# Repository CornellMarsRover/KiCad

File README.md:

# KiCad PCB Designs

This folder serves as the central repository for all KiCad PCB designs across multiple years.  
Each subfolder corresponds to a specific design cycle and contains all associated board files, schematics, and documentation.

## Notes

- All boards should be designed in **KiCad** using consistent design rules.  
- Follow best practices for manufacturability, testing, and revision tracking.  
- Keep README files updated in each yearly folder to summarize the boards within.

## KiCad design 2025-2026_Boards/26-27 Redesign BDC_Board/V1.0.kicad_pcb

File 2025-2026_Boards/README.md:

# Content for the markdown file
content = 2025-2026 Boards

This repository contains PCB designs for boards created in KiCad during the 2025-2026 design cycle.

## Overview

- **Design Tool:** KiCad  
- **Timeframe:** 2025–2026  
- **Purpose:** Centralized documentation and tracking of PCB projects made this year.

## Board Projects

- [ ] CANFD to USB board – Converts our USB connection to CANFD and vice versa to converse with the jetson
- [ ] PDB – Powers and distributes power through everything and can remotely turns on and off power to boards
- [ ] Temperature Regulation Board – Gets the temperature, displays it and turns on and off fans depending on the temperature 

## Notes

All designs should follow standard design rules and best practices for manufacturability and testing. Updates will be logged as the boards progress from schematic to layout to fabrication.

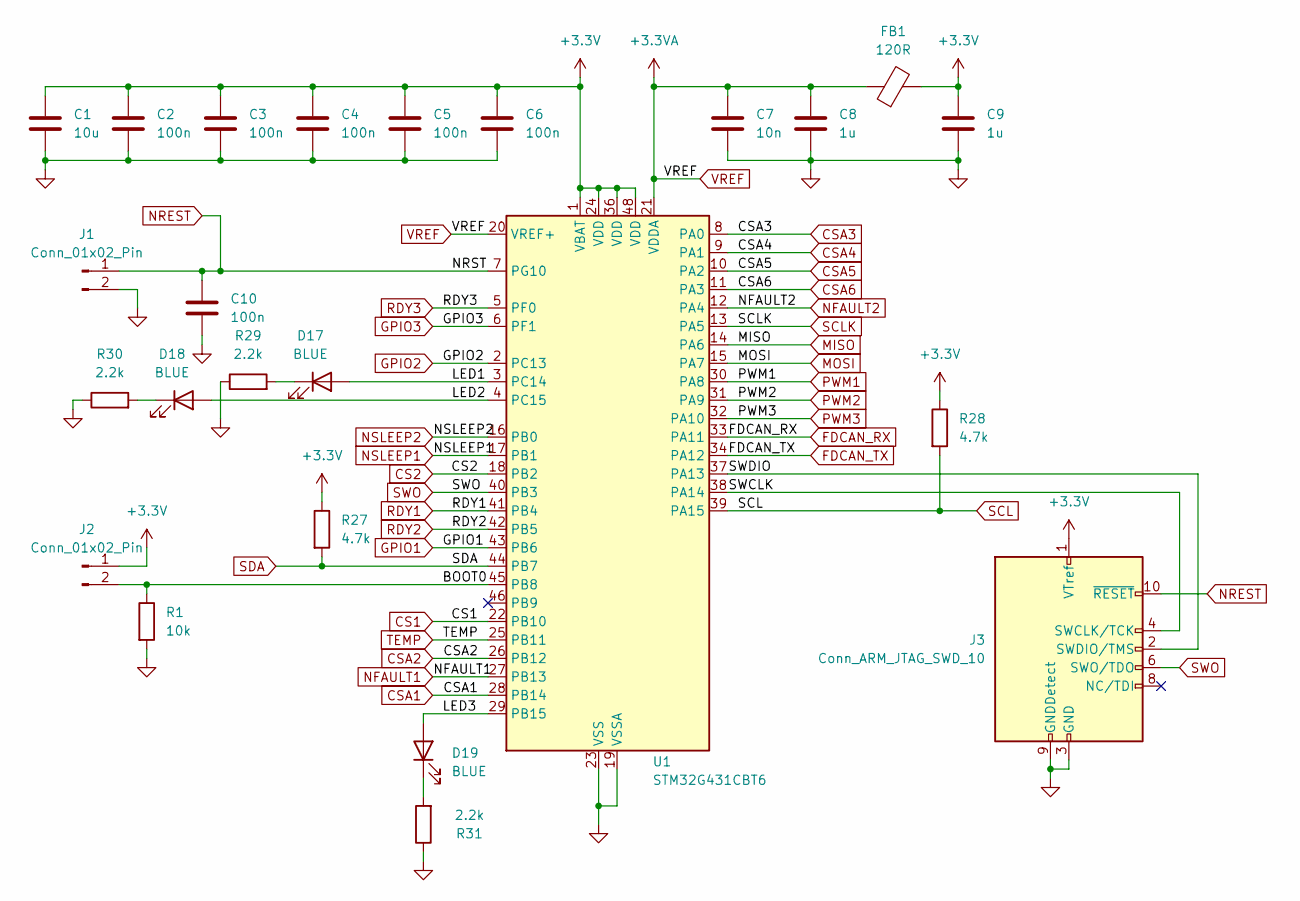
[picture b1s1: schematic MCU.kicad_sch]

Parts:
C1: 10u; C_0603_1608Metric
C2, C3, C4, C5, C6, C10: 100n; C_0402_1005Metric
C7: 10n; C_0402_1005Metric
C8, C9: 1u; C_0402_1005Metric
D17, D18, D19: BLUE; LED_0603_1608Metric
FB1: 120R; L_0603_1608Metric
J1: Conn_01x02_Pin; PinHeader_1x02_P2.54mm_Horizontal
J2: Conn_01x02_Pin; PinHeader_1x02_P2.54mm_Vertical
J3: Conn_ARM_JTAG_SWD_10; PinHeader_2x05_P1.27mm_Vertical
R1: 10k; R_0402_1005Metric
R27, R28: 4.7k; R_0402_1005Metric
R29, R30, R31: 2.2k; R_0402_1005Metric
U1: STM32G431CBT6; LQFP-48_7x7mm_P0.5mm

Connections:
+3.3V: C1.1, C2.1, C3.1, C4.1, C5.1, C6.1, C9.1, FB1.2, J2.1, J3.1 (VTref), R27.1, R28.1, U1.1 (VBAT), U1.24 (VDD), U1.36 (VDD), U1.48 (VDD); also elsewhere on the board
/MCU/BOOT0: J2.2, R1.1, U1.45 (PB8)
/MCU/LED1: D17.2 (A), U1.3 (PC14)
/MCU/LED2: D18.2 (A), U1.4 (PC15)
/MCU/LED3: D19.2 (A), U1.29 (PB15)
/MCU/SWCLK: J3.4 (SWCLK/TCK), U1.38 (PA14)
/MCU/SWDIO: J3.2 (SWDIO/TMS), U1.37 (PA13)
CS1: U1.22 (PB10); also elsewhere on the board
CS2: U1.18 (PB2); also elsewhere on the board
CSA1: U1.28 (PB14); also elsewhere on the board
CSA2: U1.26 (PB12); also elsewhere on the board
CSA3: U1.8 (PA0); also elsewhere on the board
CSA4: U1.9 (PA1); also elsewhere on the board
CSA5: U1.10 (PA2); also elsewhere on the board
CSA6: U1.11 (PA3); also elsewhere on the board
FDCAN_RX: U1.33 (PA11); also elsewhere on the board
FDCAN_TX: U1.34 (PA12); also elsewhere on the board
GND: C1.2, C2.2, C3.2, C4.2, C5.2, C6.2, C7.2, C8.2, C9.2, C10.2, J1.2, J3.3 (GND), J3.5 (GND), J3.9 (GNDDetect), R1.2, R29.1, R30.1, R31.1, U1.19 (VSSA), U1.23 (VSS), U1.35 (VSS), U1.47 (VSS); also elsewhere on the board
GPIO1: U1.43 (PB6); also elsewhere on the board
GPIO2: U1.2 (PC13); also elsewhere on the board
GPIO3: U1.6 (PF1); also elsewhere on the board
MISO: U1.14 (PA6); also elsewhere on the board
MOSI: U1.15 (PA7); also elsewhere on the board
NFAULT1: U1.27 (PB13); also elsewhere on the board
NFAULT2: U1.12 (PA4); also elsewhere on the board
NREST: C10.1, J1.1, J3.10 (~RESET), U1.7 (PG10); also elsewhere on the board
NSLEEP1: U1.17 (PB1); also elsewhere on the board
NSLEEP2: U1.16 (PB0); also elsewhere on the board
unnamed: D17.1 (K), R29.2
unnamed: D18.1 (K), R30.2
unnamed: D19.1 (K), R31.2
PWM1: U1.30 (PA8); also elsewhere on the board
PWM2: U1.31 (PA9); also elsewhere on the board
PWM3: U1.32 (PA10); also elsewhere on the board
RDY1: U1.41 (PB4); also elsewhere on the board
RDY2: U1.42 (PB5); also elsewhere on the board
RDY3: U1.5 (PF0); also elsewhere on the board
SCL: R28.2, U1.39 (PA15); also elsewhere on the board
SCLK: U1.13 (PA5); also elsewhere on the board
SDA: R27.2, U1.44 (PB7); also elsewhere on the board
SWO: J3.6 (SWO/TDO), U1.40 (PB3)
TEMP: U1.25 (PB11); also elsewhere on the board
VREF: C7.1, C8.1, FB1.1, U1.20 (VREF+), U1.21 (VDDA)

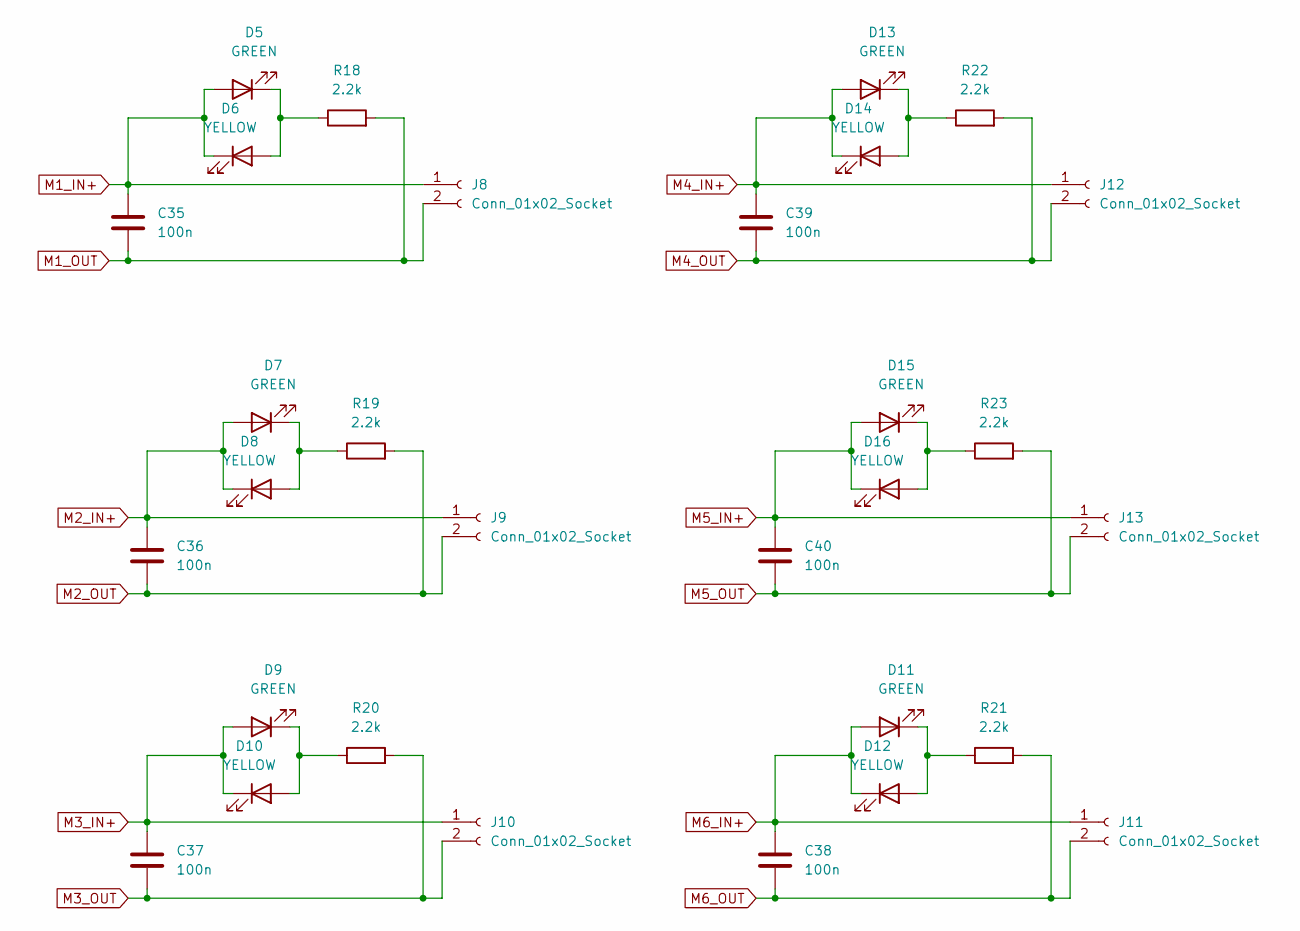
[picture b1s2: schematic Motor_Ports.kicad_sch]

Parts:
C35, C36, C37, C38, C39, C40: 100n; C_1206_3216Metric
D5, D7, D9, D11, D13, D15: GREEN; LED_0603_1608Metric
D6, D8, D10, D12, D14, D16: YELLOW; LED_0603_1608Metric
J8, J9, J10, J11, J12, J13: Conn_01x02_Socket; AMASS_XT30PW-M_1x02_P2.50mm_Horizontal
R18, R19, R20, R21, R22, R23: 2.2k; R_0402_1005Metric

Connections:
M1_IN+: C35.1, D5.2 (A), D6.1 (K), J8.1; also elsewhere on the board
M1_OUT: C35.2, J8.2, R18.2; also elsewhere on the board
M2_IN+: C36.1, D7.2 (A), D8.1 (K), J9.1; also elsewhere on the board
M2_OUT: C36.2, J9.2, R19.2; also elsewhere on the board
M3_IN+: C37.1, D9.2 (A), D10.1 (K), J10.1; also elsewhere on the board
M3_OUT: C37.2, J10.2, R20.2; also elsewhere on the board
M4_IN+: C39.1, D13.2 (A), D14.1 (K), J12.1; also elsewhere on the board
M4_OUT: C39.2, J12.2, R22.2; also elsewhere on the board
M5_IN+: C40.1, D15.2 (A), D16.1 (K), J13.1; also elsewhere on the board
M5_OUT: C40.2, J13.2, R23.2; also elsewhere on the board
M6_IN+: C38.1, D11.2 (A), D12.1 (K), J11.1; also elsewhere on the board
M6_OUT: C38.2, J11.2, R21.2; also elsewhere on the board
unnamed: D5.1 (K), D6.2 (A), R18.1
unnamed: D7.1 (K), D8.2 (A), R19.1
unnamed: D9.1 (K), D10.2 (A), R20.1
unnamed: D11.1 (K), D12.2 (A), R21.1
unnamed: D13.1 (K), D14.2 (A), R22.1
unnamed: D15.1 (K), D16.2 (A), R23.1

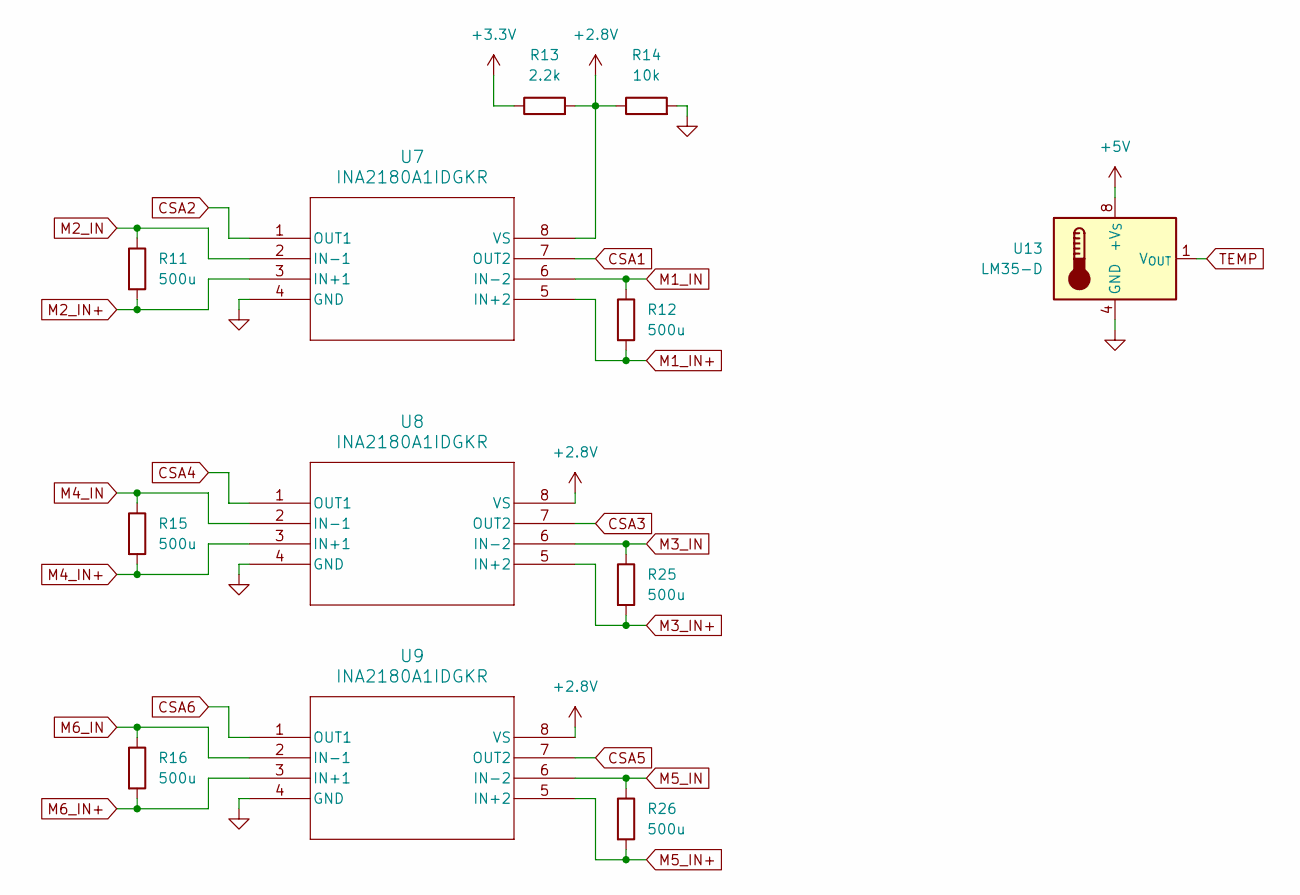
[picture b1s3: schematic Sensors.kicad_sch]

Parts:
R11, R12, R15, R16, R25, R26: 500u; R_0805_2012Metric
R13: 2.2k; R_0402_1005Metric
R14: 10k; R_0402_1005Metric
U7, U8, U9: INA2180A1IDGKR; VSSOP-8_3x3mm_P0.65mm
U13: LM35-D; SOIC-8_3.9x4.9mm_P1.27mm

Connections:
+2.8V: R13.2, R14.1, U7.8 (VS), U8.8 (VS), U9.8 (VS)
+3.3V: R13.1; also elsewhere on the board
+5V: U13.8 (+V_{S}); also elsewhere on the board
CSA1: U7.7 (OUT2); also elsewhere on the board
CSA2: U7.1 (OUT1); also elsewhere on the board
CSA3: U8.7 (OUT2); also elsewhere on the board
CSA4: U8.1 (OUT1); also elsewhere on the board
CSA5: U9.7 (OUT2); also elsewhere on the board
CSA6: U9.1 (OUT1); also elsewhere on the board
GND: R14.2, U7.4 (GND), U8.4 (GND), U9.4 (GND), U13.4 (GND); also elsewhere on the board
M1_IN: R12.1, U7.6 (IN-2); also elsewhere on the board
M1_IN+: R12.2, U7.5 (IN+2); also elsewhere on the board
M2_IN: R11.1, U7.2 (IN-1); also elsewhere on the board
M2_IN+: R11.2, U7.3 (IN+1); also elsewhere on the board
M3_IN: R25.1, U8.6 (IN-2); also elsewhere on the board
M3_IN+: R25.2, U8.5 (IN+2); also elsewhere on the board
M4_IN: R15.1, U8.2 (IN-1); also elsewhere on the board
M4_IN+: R15.2, U8.3 (IN+1); also elsewhere on the board
M5_IN: R26.1, U9.6 (IN-2); also elsewhere on the board
M5_IN+: R26.2, U9.5 (IN+2); also elsewhere on the board
M6_IN: R16.1, U9.2 (IN-1); also elsewhere on the board
M6_IN+: R16.2, U9.3 (IN+1); also elsewhere on the board
TEMP: U13.1 (V_{OUT}); also elsewhere on the board

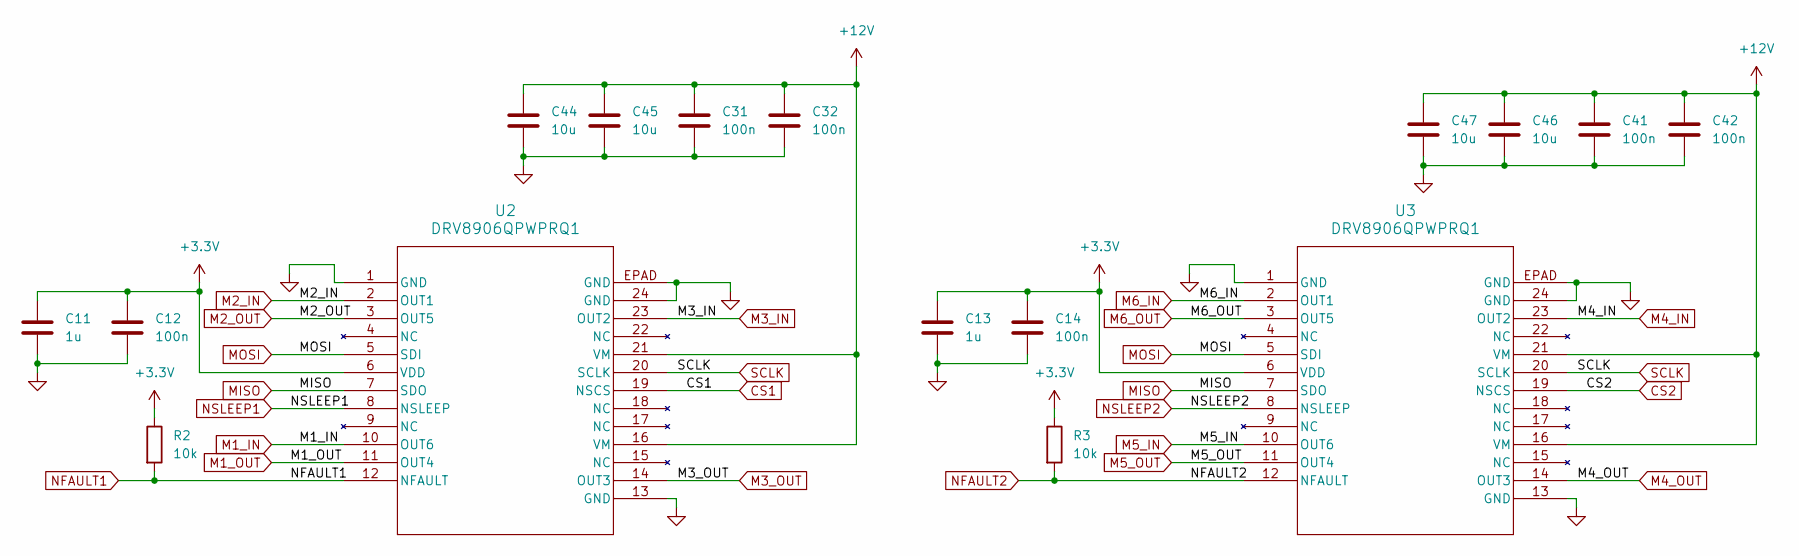
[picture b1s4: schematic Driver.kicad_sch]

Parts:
C11, C13: 1u; C_0402_1005Metric
C12, C14, C31, C32, C41, C42: 100n; C_0402_1005Metric
C44, C45, C46, C47: 10u; C_0603_1608Metric
R2, R3: 10k; R_0402_1005Metric
U2, U3: DRV8906QPWPRQ1; HTSSOP24_PWP_TEX

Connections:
+3.3V: C11.1, C12.1, C13.1, C14.1, R2.1, R3.1, U2.6 (VDD), U3.6 (VDD); also elsewhere on the board
+12V: C31.1, C32.1, C41.1, C42.1, C44.1, C45.1, C46.1, C47.1, U2.16 (VM), U2.21 (VM), U3.16 (VM), U3.21 (VM); also elsewhere on the board
CS1: U2.19 (NSCS); also elsewhere on the board
CS2: U3.19 (NSCS); also elsewhere on the board
GND: C11.2, C12.2, C13.2, C14.2, C31.2, C32.2, C41.2, C42.2, C44.2, C45.2, C46.2, C47.2, U2.1 (GND), U2.13 (GND), U2.24 (GND), U2.EPAD (GND), U3.1 (GND), U3.13 (GND), U3.24 (GND), U3.EPAD (GND); also elsewhere on the board
M1_IN: U2.10 (OUT6); also elsewhere on the board
M1_OUT: U2.11 (OUT4); also elsewhere on the board
M2_IN: U2.2 (OUT1); also elsewhere on the board
M2_OUT: U2.3 (OUT5); also elsewhere on the board
M3_IN: U2.23 (OUT2); also elsewhere on the board
M3_OUT: U2.14 (OUT3); also elsewhere on the board
M4_IN: U3.23 (OUT2); also elsewhere on the board
M4_OUT: U3.14 (OUT3); also elsewhere on the board
M5_IN: U3.10 (OUT6); also elsewhere on the board
M5_OUT: U3.11 (OUT4); also elsewhere on the board
M6_IN: U3.2 (OUT1); also elsewhere on the board
M6_OUT: U3.3 (OUT5); also elsewhere on the board
MISO: U2.7 (SDO), U3.7 (SDO); also elsewhere on the board
MOSI: U2.5 (SDI), U3.5 (SDI); also elsewhere on the board
NFAULT1: R2.2, U2.12 (NFAULT); also elsewhere on the board
NFAULT2: R3.2, U3.12 (NFAULT); also elsewhere on the board
NSLEEP1: U2.8 (NSLEEP); also elsewhere on the board
NSLEEP2: U3.8 (NSLEEP); also elsewhere on the board
SCLK: U2.20 (SCLK), U3.20 (SCLK); also elsewhere on the board

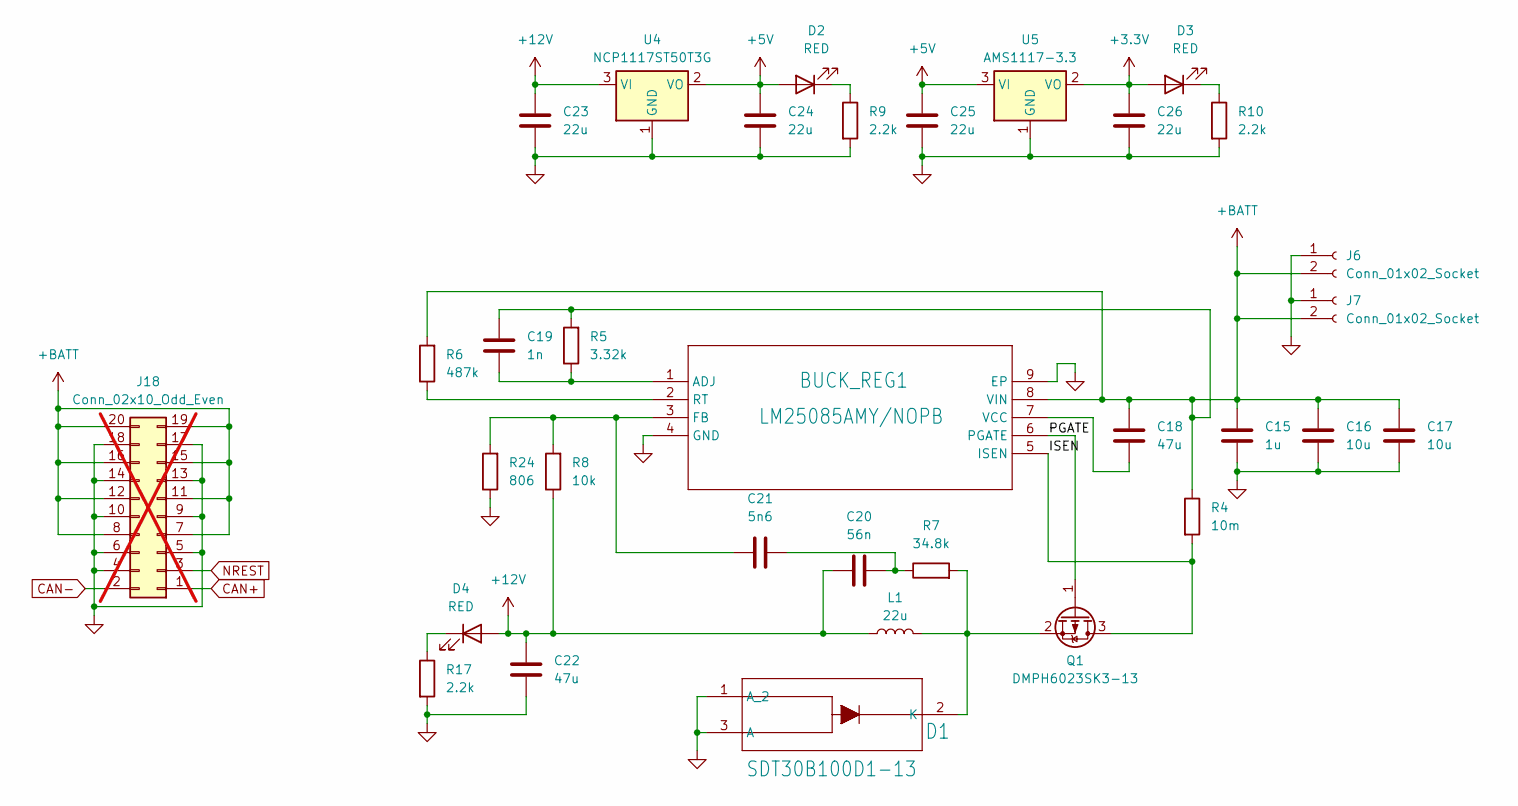
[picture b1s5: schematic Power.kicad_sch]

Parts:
BUCK_REG1: LM25085AMY/NOPB; HVSSOP-8-1EP_3x3mm_P0.65mm_EP1.57x1.89mm
C15: 1u; C_0603_1608Metric
C16, C17: 10u; C_1206_3216Metric
C18, C22: 47u; C_1206_3216Metric
C19: 1n; C_0603_1608Metric
C20: 56n; C_0603_1608Metric
C21: 5n6; C_0603_1608Metric
C23, C24, C25, C26: 22u; C_0805_2012Metric
D1: SDT30B100D1-13; TO-252-2
D2, D3, D4: RED; LED_0603_1608Metric
J6, J7: Conn_01x02_Socket; AMASS_XT30PW-M_1x02_P2.50mm_Horizontal
J18: Conn_02x10_Odd_Even; PinSocket_2x10_P2.54mm_Horizontal; not fitted
L1: 22u; IND_A-4R7M
Q1: DMPH6023SK3-13; TO-252-2
R4: 10m; R_1206_3216Metric
R5: 3.32k; R_1206_3216Metric
R6: 487k; R_0603_1608Metric
R7: 34.8k; R_0603_1608Metric
R8: 10k; R_0603_1608Metric
R9, R10, R17: 2.2k; R_0402_1005Metric
R24: 806; R_0603_1608Metric
U4: NCP1117ST50T3G; SOT-223-3_TabPin2
U5: AMS1117-3.3; SOT-223-3_TabPin2

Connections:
+3.3V: C26.1, D3.2 (A), U5.2 (VO); also elsewhere on the board
+5V: C24.1, C25.1, D2.2 (A), U4.2 (VO), U5.3 (VI); also elsewhere on the board
+12V: C20.1, C22.1, C23.1, D4.2 (A), L1.1, R8.1, U4.3 (VI); also elsewhere on the board
+BATT: BUCK_REG1.8 (VIN), C15.1, C16.1, C17.1, C18.1, C19.1, J6.2, J7.2, J18.7, J18.8, J18.11, J18.12, J18.15, J18.16, J18.19, J18.20, R4.1, R5.2, R6.2
/Power/PGATE: BUCK_REG1.6 (PGATE), Q1.1 (G)
CAN+: J18.1; also elsewhere on the board
CAN-: J18.2; also elsewhere on the board
GND: BUCK_REG1.4 (GND), BUCK_REG1.9 (EP), C15.2, C16.2, C17.2, C22.2, C23.2, C24.2, C25.2, C26.2, D1.1 (A_2), D1.3 (A), J6.1, J7.1, J18.4, J18.5, J18.6, J18.9, J18.10, J18.13, J18.14, J18.17, J18.18, R9.2, R10.2, R17.2, R24.1, U4.1 (GND), U5.1 (GND); also elsewhere on the board
NREST: J18.3; also elsewhere on the board
unnamed: BUCK_REG1.1 (ADJ), C19.2, R5.1
unnamed: BUCK_REG1.3 (FB), C21.1, R8.2, R24.2
unnamed: BUCK_REG1.2 (RT), R6.1
unnamed: BUCK_REG1.7 (VCC), C18.2
unnamed: C20.2, C21.2, R7.1
unnamed: D2.1 (K), R9.1
unnamed: D3.1 (K), R10.1
unnamed: D4.1 (K), R17.1

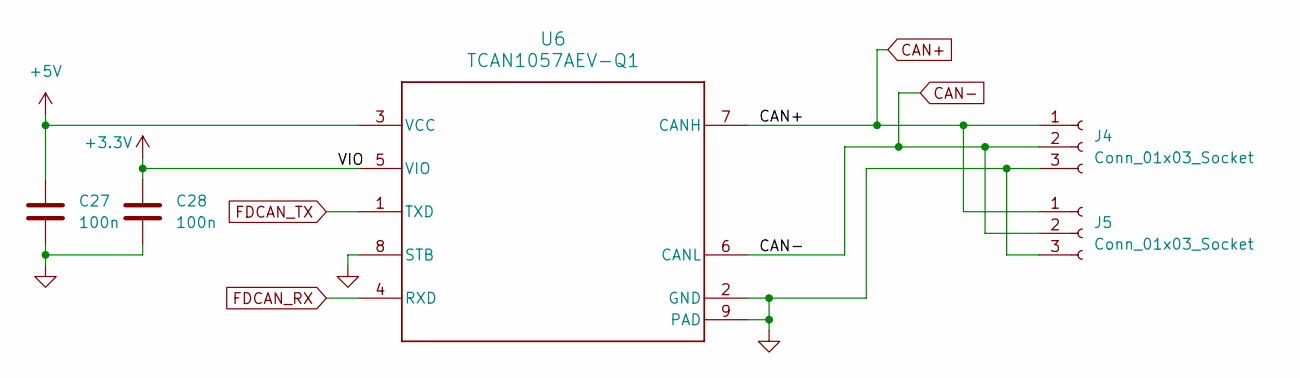
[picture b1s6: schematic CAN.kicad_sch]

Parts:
C27, C28: 100n; C_0402_1005Metric
J4, J5: Conn_01x03_Socket; JST_PH_S3B-PH-SM4-TB_1x03-1MP_P2.00mm_Horizontal
U6: TCAN1057AEV-Q1; SOIC-8_3.9x4.9mm_P1.27mm; MPN TCAN1057AEVDRQ1

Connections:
+3.3V: C28.1, U6.5 (VIO); also elsewhere on the board
+5V: C27.1, U6.3 (VCC); also elsewhere on the board
CAN+: J4.1, J5.1, U6.7 (CANH); also elsewhere on the board
CAN-: J4.2, J5.2, U6.6 (CANL); also elsewhere on the board
FDCAN_RX: U6.4 (RXD); also elsewhere on the board
FDCAN_TX: U6.1 (TXD); also elsewhere on the board
GND: C27.2, C28.2, J4.3, J5.3, U6.2 (GND), U6.8 (STB), U6.9 (PAD); also elsewhere on the board

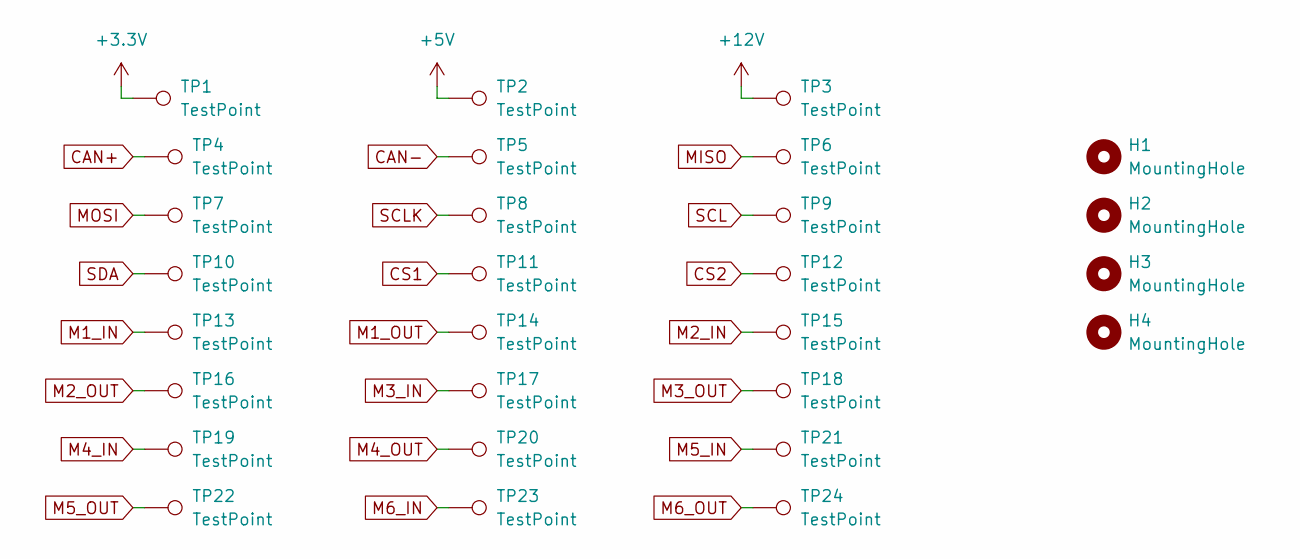
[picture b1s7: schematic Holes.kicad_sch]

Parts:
H1, H2, H3, H4: MountingHole; MountingHole_3.2mm_M3
TP1, TP2, TP3, TP4, TP5, TP6, TP7, TP8, TP9, TP10, TP11, TP12, TP13, TP14, TP15, TP16, TP17, TP18, TP19, TP20, TP21, TP22, TP23, TP24: TestPoint; TestPoint_Pad_D1.0mm

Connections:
+3.3V: TP1.1 (1_1); also elsewhere on the board
+5V: TP2.1 (1_1); also elsewhere on the board
+12V: TP3.1 (1_1); also elsewhere on the board
CAN+: TP4.1 (1_1); also elsewhere on the board
CAN-: TP5.1 (1_1); also elsewhere on the board
CS1: TP11.1 (1_1); also elsewhere on the board
CS2: TP12.1 (1_1); also elsewhere on the board
M1_IN: TP13.1 (1_1); also elsewhere on the board
M1_OUT: TP14.1 (1_1); also elsewhere on the board
M2_IN: TP15.1 (1_1); also elsewhere on the board
M2_OUT: TP16.1 (1_1); also elsewhere on the board
M3_IN: TP17.1 (1_1); also elsewhere on the board
M3_OUT: TP18.1 (1_1); also elsewhere on the board
M4_IN: TP19.1 (1_1); also elsewhere on the board
M4_OUT: TP20.1 (1_1); also elsewhere on the board
M5_IN: TP21.1 (1_1); also elsewhere on the board
M5_OUT: TP22.1 (1_1); also elsewhere on the board
M6_IN: TP23.1 (1_1); also elsewhere on the board
M6_OUT: TP24.1 (1_1); also elsewhere on the board
MISO: TP6.1 (1_1); also elsewhere on the board
MOSI: TP7.1 (1_1); also elsewhere on the board
SCL: TP9.1 (1_1); also elsewhere on the board
SCLK: TP8.1 (1_1); also elsewhere on the board
SDA: TP10.1 (1_1); also elsewhere on the board

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
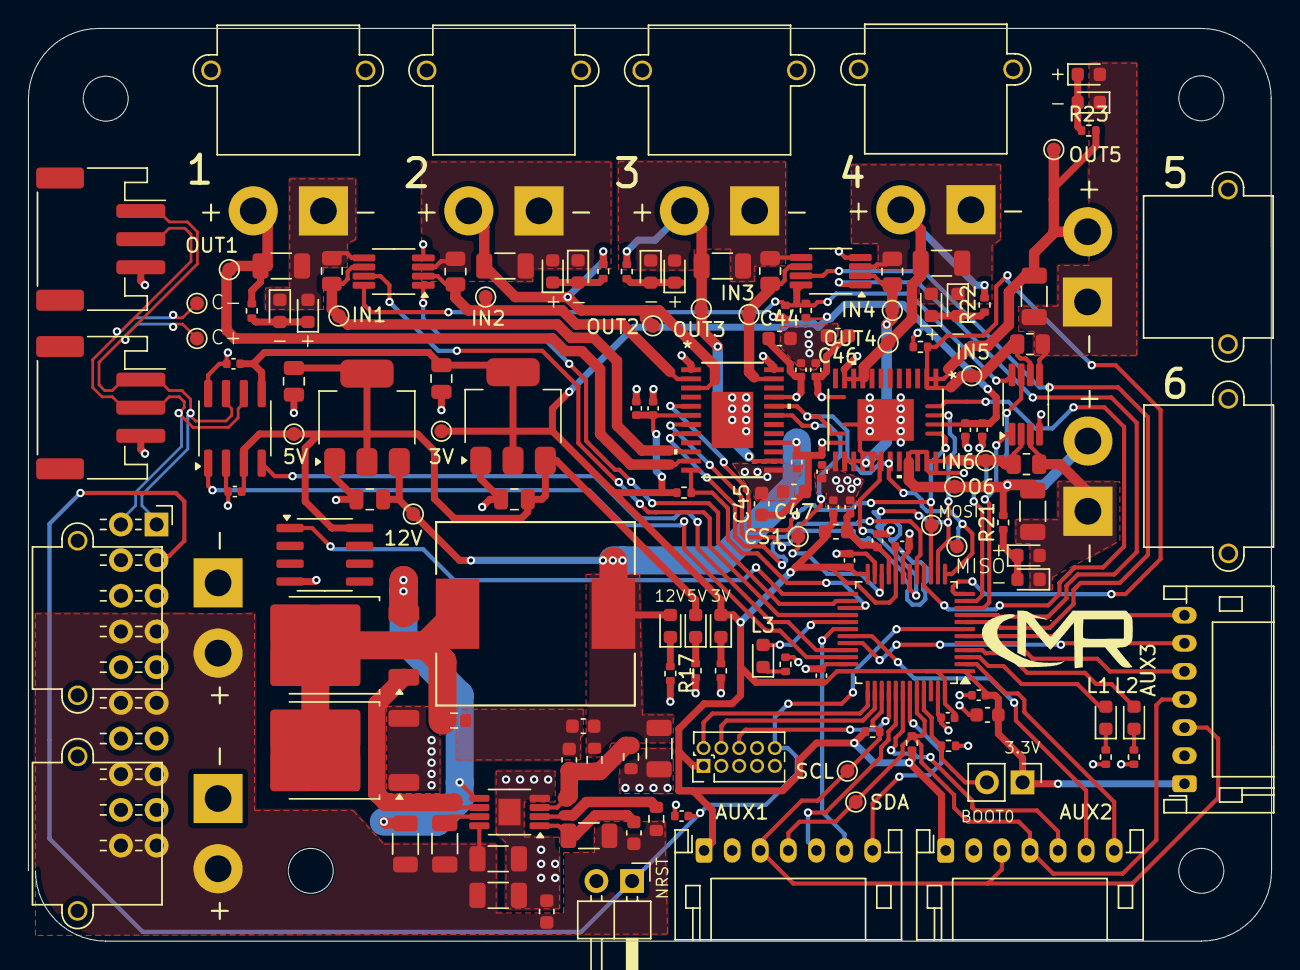
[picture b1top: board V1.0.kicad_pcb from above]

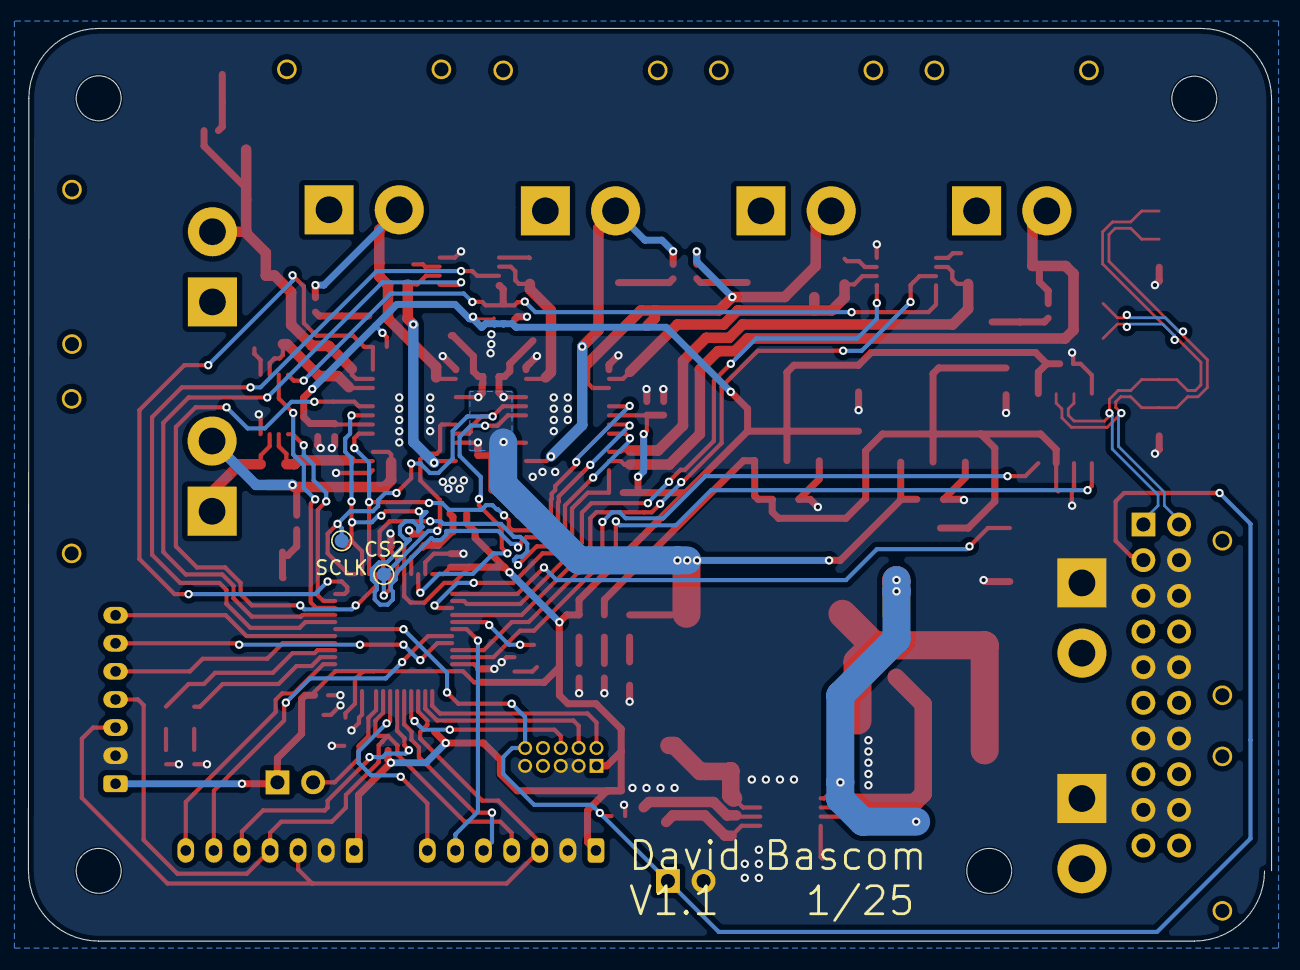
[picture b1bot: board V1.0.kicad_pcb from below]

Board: 2 copper layers, 88.5 x 65.0 mm, 151 parts (2 on the bottom side), 84 nets.

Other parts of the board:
J14, J15, J16: Conn_01x07_Socket; JST_PH_S7B-PH-K_1x07_P2.00mm_Horizontal

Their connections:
+3.3V: J14.1, J15.1, J16.1; also elsewhere on the board
GND: J14.2, J15.2, J16.2; also elsewhere on the board
GPIO1: J14.7; also elsewhere on the board
GPIO2: J15.7; also elsewhere on the board
GPIO3: J16.7; also elsewhere on the board
PWM1: J14.6; also elsewhere on the board
PWM2: J15.6; also elsewhere on the board
PWM3: J16.6; also elsewhere on the board
RDY1: J14.5; also elsewhere on the board
RDY2: J15.5; also elsewhere on the board
RDY3: J16.5; also elsewhere on the board
SCL: J14.3, J15.3, J16.3; also elsewhere on the board
SDA: J14.4, J15.4, J16.4; also elsewhere on the board

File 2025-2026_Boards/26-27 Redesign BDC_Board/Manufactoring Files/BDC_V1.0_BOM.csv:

,,,xxxx xxxx xxxxx xxPCS BOM  ,,,122,,
,,,,,,,,
,,,,,,,,
,,,,,,,,
Item #,*Designator,*Qty,Manufacturer,*Mfg Part #,Description / Value,*Package/Footprint ,Type,Your Instructions / Notes
1,BUCK_REG1,1,Texas Instruments,LM25085AMY/NOPB,Buck Converter,8-HVSSOP,SMD,
2,C1,1,Samsung Electro-Mechanics,CL10A106MQ8NNNC,10uF Capacitor,0603,SMD,
3,"C2-C6, C10, C12, C14, C27, C28, C31, C32, C41, C42",14,Samsung Electro-Mechanics,CL05B104KP5NNNC,100nF Capacitor,0402,SMD,
4,C7,1,Samsung Electro-Mechanics,CL05B103KB5NNNC,10nF Capacitor,0402,SMD,
5,"C8, C9, C11, C13, C29, C30, C33, C34",8,Samsung Electro-Mechanics,CL05A104KA5NNNC,1uF Capacitor,0402,SMD,
6,C15,1,Samsung Electro-Mechanics,CL10A105KB8NNNC,1uF Capacitor,0603,SMD,
7,"C16, C17",2,Samsung Electro-Mechanics,CL31A106MBHNNNE,10uF Capacitor,1206,SMD,
8,"C18, C22",2,Taiyo Yuden,EMK316BBJ476ML-T,47uF Capacitor,1206,SMD,
9,C19,1,Samsung Electro-Mechanics,CL31A476MPHNNNE,1nF Capacitor,0603,SMD,
10,C20,1,KYOCERA AVX,KAM15AR71C563KT,56nF Capacitor,0603,SMD,
11,C21,1,KYOCERA AVX,KGM15AR71H562KM,5.6nF Capacitor,0603,SMD,
12,C23-C26,4,Samsung Electro-Mechanics,CL21A226MQQNNNE,22uF Capacitor,0805,SMD,
13,C35-C40,6,Samsung Electro-Mechanics,CL31B104KBCNNNC,100nF Capacitor,1206,SMD,
14,D1,1,Diodes Incorporated,SDT30B100D1-13,DIODE SCHOTTKY 100V 30A TO252-3,TO-252-3,SMD,
15,"D2, D3, D4",3,Lite-On Inc.,LTST-C193KRKT-5A,Red LED,0603,SMD,
16,"D5, D7, D9, D11, D13, D15",6,Lite-On Inc.,LTST-C193KGKT-5A,Green LED,0603,SMD,
17,"D6, D8, D10, D12, D14, D16",6,Lite-On Inc.,LTST-C193KSKT-5A,Yellow LED,0603,SMD,
18,"D17, D18, D19",3,Lite-On Inc.,LTST-C193TBKT-5A,Blue LED,0603,SMD,
19,FB1,1,Murata Electronics,BLM18KG121TN1D,120 Ohms @ 100MHz Ferrite Bead,0603,SMD,
20,"J1, J2",2,Würth Elektronik,61300211121,CONN HEADER VERT 2POS 2.54MM,1x2_P2.54mm,THT,
21,J3,1,Sullins Connector Solutions,GRPB052VWVN-RC,CONN HEADER VERT 10POS 1.27MM,2x5_P1.27mm,THT,
22,"J4, J5",2,JST Sales America Inc.,S3B-PH-SM4-TB,CONN HEADER SMD R/A 3POS 2MM,1x03-1MP_P2.00mm_Horizontal,SMD,
23,J6-J13,8,AMASS,XT30PW-M,XT30 Connector,1x02_P2.50mm_Horizontal,THT,
24,"J14, J15, J16",3,JST Sales America Inc.,S7B-PH-K-S,CONN HEADER R/A 7POS 2MM,1x07_P2.00mm_Horizontal,THT,
25,L1,1,Bourns Inc.,SRP1265A-220M,22uH Inductor,Non-Standard,SMD,
26,Q1,1,Diodes Incorporated,DMPH6023SK3-13,P-Channel Mosfet,TO-252-3,SMD,
27,"R1, R2, R3, R14",4,Samsung Electro-Mechanics,RC1005F103CS,10k Resistor,0402,SMD,
28,R4,1,Panasonic Electronic Components,ERJ-8CWFR010V,10m Resistor,1206,SMD,
29,R5,1,Bourns Inc.,CR1206-FX-3321ELF,3.32k Resistor,1206,SMD,
30,R6,1,YAGEO,RC0603FR-07487KL,487k Resistor,0603,SMD,
31,R7,1,YAGEO,RC0603FR-0734K8L,34.8k Resistor,0603,SMD,
32,R8,1,TE Connectivity Passive Product,CRGH0603J10K,10k Resistor,0603,SMD,
33,"R9, R10",2,YAGEO,RC0402FR-071KL,1k Resistor,0402,SMD,
34,"R11, R12, R15, R16, R25, R26",6,Stackpole Electronics Inc,CSSH0805FTL500,500u Resistor,0805,SMD,
35,"R13, R29, R30, R31",4,YAGEO,RC0402FR-072K2L,2.2k Resistor,0402,SMD,
36,R17 - R23,7,Stackpole Electronics Inc,RMCF0603JT2K20,2.2k Resistor,0603,SMD,
37,R24,1,Vishay Dale,CRCW0603806RFKEAC,806 Ohm Resistor,0603,SMD,
38,"R27, R28",2,YAGEO,RC0402FR-074K7L,4.7k Resistor,0402,SMD,
39,U1,1,STMicroelectronics,STM32G431CBT7,Microcontroller,LQFP-48_7x7mm_P0.5mm,SMD,
40,"U2, U3",2,Texas Instruments,DRV8906QPWPRQ1,Motor Driver,24-HTSSOP,SMD,
41,U4,1,onsemi,NCP1117ST50T3G,5V Regulator,SOT-223,SMD,
42,U5,1,UMW,AMS1117-3.3,3.3V Regulator,SOT-223-3_TabPin3,SMD,
43,U6,1,Texas Instruments,TCAN1057AEVDRQ1,FDCAN Transiever,SOIC-8_3.9x4.9mm_P1.27mm,SMD,
44,"U7, U8, U9",3,Texas Instruments,INA2180A1IDGKR,Current Sensor,8-VSSOP,SMD,
45,U13,1,Microchip Technology,MCP9700T-E/TT,Temp Sensor,SOT-23-3,SMD,
,,,,,,,,
,,,,,,,,
,,,,,,,,
,,,,,,,,
,,,,,,,,
,,,,,,,,
,,,,,,,,
,,,,,,,,
,,,,,,,,
,,,,,,,,
,,,,,,,,
,,,,,,,,
,,,,,,,,
,,,,,,,,
,,,,,,,,
,,,,,,,,
,,,,,,,,
,,,,,,,,
,,,,,,,,
